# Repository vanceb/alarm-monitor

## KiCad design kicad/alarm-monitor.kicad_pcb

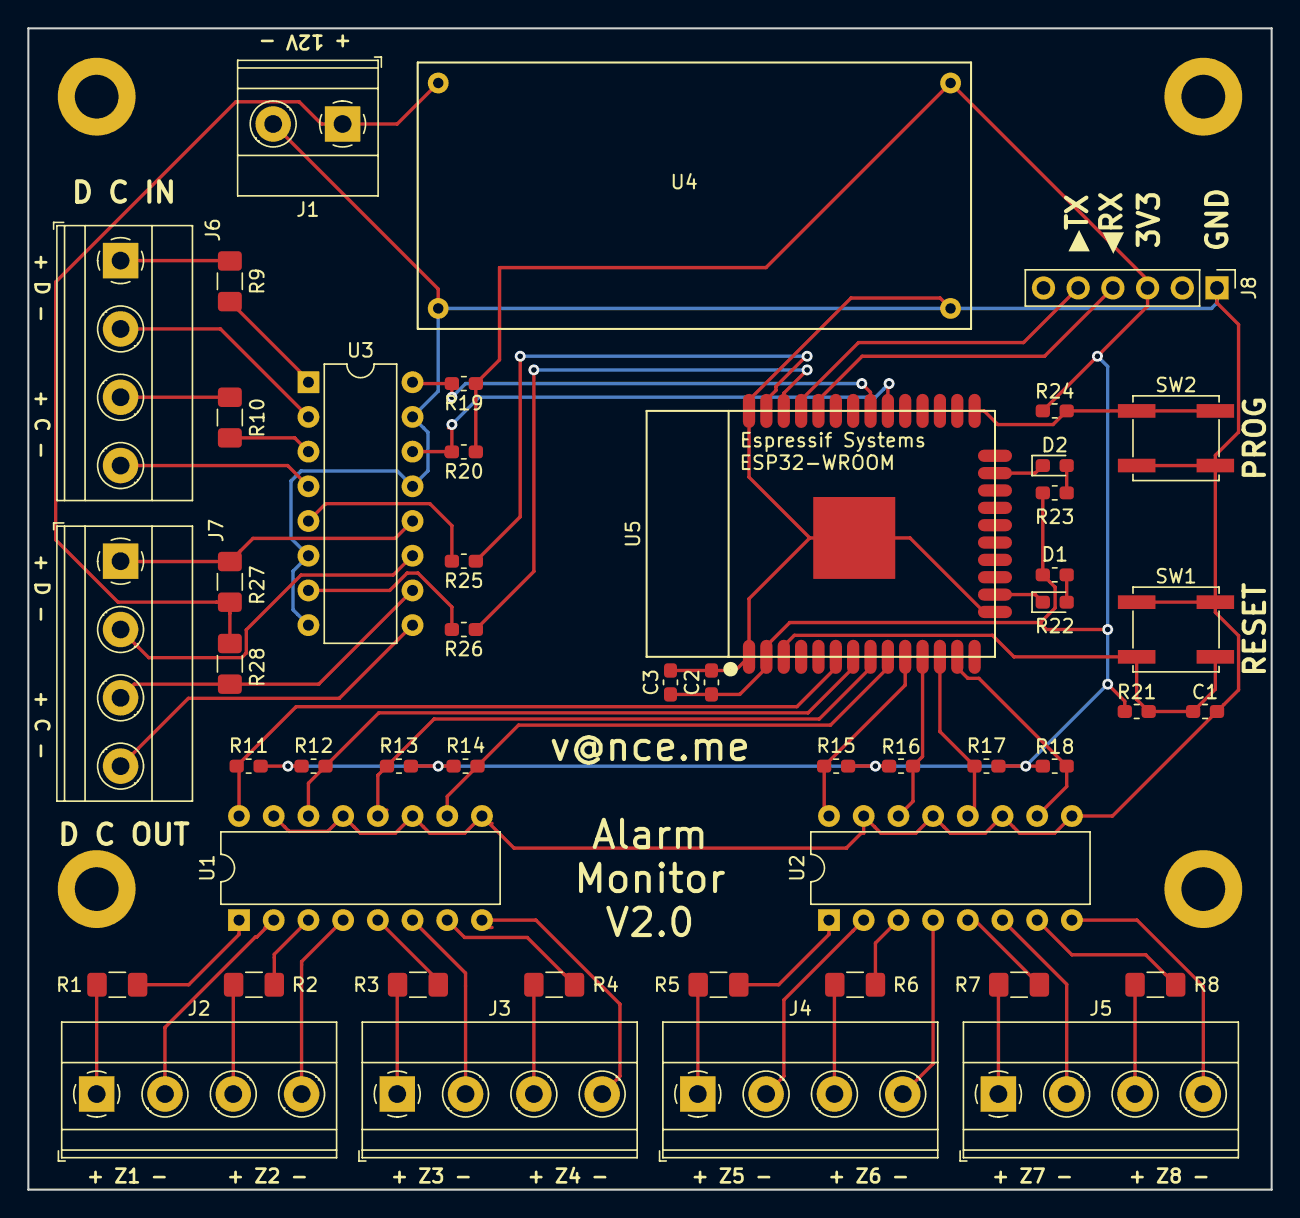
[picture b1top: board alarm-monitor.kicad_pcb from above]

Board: 2 copper layers, 91.0 x 85.0 mm, 48 parts (0 on the bottom side), 59 nets.

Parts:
C1: 1uF; C_0603_1608Metric_Pad1.05x0.95mm_HandSolder
C2: 10uF; C_0603_1608Metric_Pad1.05x0.95mm_HandSolder
C3: 0.1uF; C_0603_1608Metric_Pad1.05x0.95mm_HandSolder
D1, D2: LED; LED_0603_1608Metric_Pad1.05x0.95mm_HandSolder
J1: Power; TerminalBlock_Phoenix_MKDS-1,5-2-5.08_1x02_P5.08mm_Horizont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
J2: Z1 Z2; TerminalBlock_Phoenix_MKDS-1,5-4_1x04_P5.00mm_Horizontal
J3: Z3 Z4; TerminalBlock_Phoenix_MKDS-1,5-4_1x04_P5.00mm_Horizontal
J4: Z5 Z6; TerminalBlock_Phoenix_MKDS-1,5-4_1x04_P5.00mm_Horizontal
J5: Z7 Z8; TerminalBlock_Phoenix_MKDS-1,5-4_1x04_P5.00mm_Horizontal
J6: DIN CIN; TerminalBlock_Phoenix_MKDS-1,5-4_1x04_P5.00mm_Horizontal
J7: DOUT COUT; TerminalBlock_Phoenix_MKDS-1,5-4_1x04_P5.00mm_Horizontal
J8: SERIAL; PinHeader_1x06_P2.54mm_Vertical
R1, R2, R3, R4, R5, R6, R7, R8, R9, R10, R27, R28: 680; R_1206_3216Metric_Pad1.42x1.75mm_HandSolder
R11, R12, R13, R14, R15, R16, R17, R18, R19, R20, R21, R24: 10k; R_0603_1608Metric_Pad1.05x0.95mm_HandSolder
R22, R23: 330; R_0603_1608Metric_Pad1.05x0.95mm_HandSolder
R25, R26: 100; R_0603_1608Metric_Pad1.05x0.95mm_HandSolder
SW1: RESET; SW_SPST_EVPBF
SW2: PROG; SW_SPST_EVPBF
U1, U2, U3: LTV-847; DIP-16_W7.62mm
U4: Buck_Converter
U5: ESP32-WROOM

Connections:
+3V3: C2.1, C3.1, J8.3, R11.1, R12.1, R13.1, R14.1, R15.1, R16.1, R17.1, R18.1, R19.1, R20.1, R21.1, R22.2, R23.2, R24.1, U4.3, U5.2
+12V: J1.1, R27.2, R28.2, U4.1
CLK_IN: R20.2, U3.14, U5.30
CLK_OUT: R26.1, U5.36
DATA_IN: R19.2, U3.16, U5.31
DATA_OUT: R25.1, U5.37
GND: C1.2, C2.2, C3.2, J1.2, J8.1, SW1.1, SW2.2, U1.9, U1.11, U1.13, U1.15, U2.9, U2.11, U2.13, U2.15, U3.6, U3.8, U3.13, U3.15, U4.2, U4.4, U5.1, U5.15, U5.38, U5.39
unnamed: C1.1, R21.2, SW1.2, U5.3
unnamed: D1.1, U5.16
unnamed: D1.2, R22.1
unnamed: D2.1, U5.23
unnamed: D2.2, R23.1
unnamed: J2.1, R1.2
unnamed: J2.2, U1.2
unnamed: J2.3, R2.2
unnamed: J2.4, U1.4
unnamed: J3.1, R3.2
unnamed: J3.2, U1.6
unnamed: J3.3, R4.2
unnamed: J3.4, U1.8
unnamed: J4.1, R5.2
unnamed: J4.2, U2.2
unnamed: J4.3, R6.2
unnamed: J4.4, U2.4
unnamed: J5.1, R7.2
unnamed: J5.2, U2.6
unnamed: J5.3, R8.2
unnamed: J5.4, U2.8
unnamed: J6.1, R9.2
unnamed: J6.2, U3.2
unnamed: J6.3, R10.2
unnamed: J6.4, U3.4
unnamed: J7.1, R27.1, U3.12
unnamed: J7.2, U3.11
unnamed: J7.3, R28.1, U3.10
unnamed: J7.4, U3.9
unnamed: R1.1, U1.1
unnamed: R2.1, U1.3
unnamed: R3.1, U1.5
unnamed: R4.1, U1.7
unnamed: R5.1, U2.1
unnamed: R6.1, U2.3
unnamed: R7.1, U2.5
unnamed: R8.1, U2.7
unnamed: R9.1, U3.1
unnamed: R10.1, U3.3
unnamed: R24.2, SW2.1, U5.25
unnamed: R25.2, U3.5
unnamed: R26.2, U3.7
RXDI: J8.4, U5.34
TXDO: J8.5, U5.35
ZONE1: R11.2, U1.16, U5.6
ZONE2: R12.2, U1.14, U5.7
ZONE3: R13.2, U1.12, U5.8
ZONE4: R14.2, U1.10, U5.9
ZONE5: R15.2, U2.16, U5.10
ZONE6: R16.2, U2.14, U5.11
ZONE7: R17.2, U2.12, U5.12
ZONE8: R18.2, U2.10, U5.13
